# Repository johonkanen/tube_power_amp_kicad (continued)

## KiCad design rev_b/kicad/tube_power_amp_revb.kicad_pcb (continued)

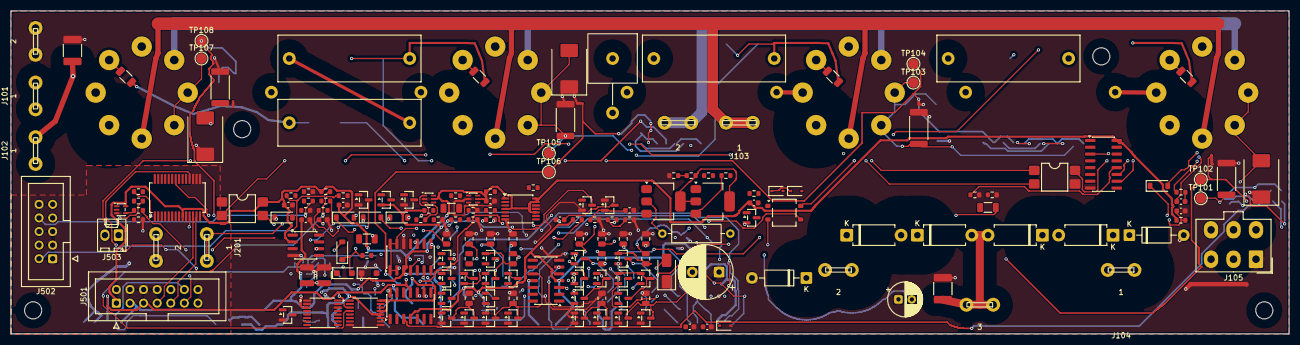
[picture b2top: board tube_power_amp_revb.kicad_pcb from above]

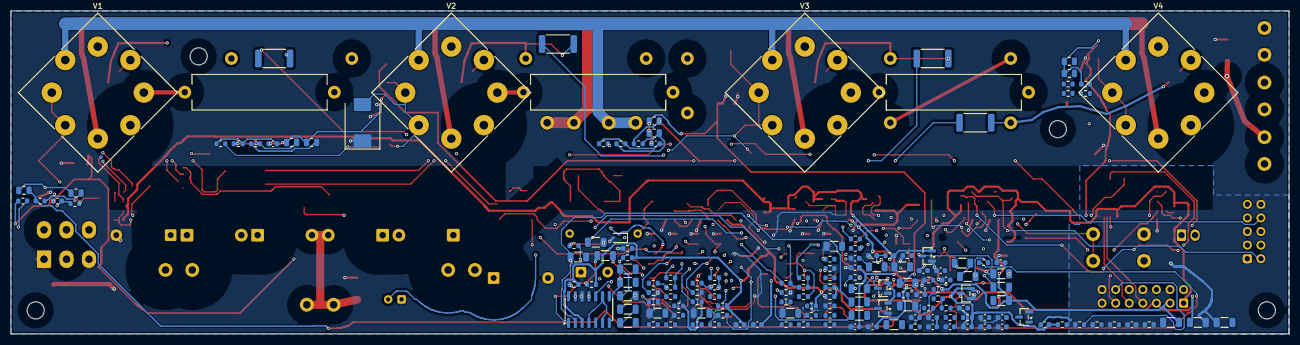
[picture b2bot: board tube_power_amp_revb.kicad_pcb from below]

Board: 4 copper layers, 238.8 x 60.3 mm, 340 parts (158 on the bottom side), 188 nets.

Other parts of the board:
H1, H2, H3, H4: M3 standoff 15 mm

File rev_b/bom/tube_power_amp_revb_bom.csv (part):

refs,qty,value,footprint,candidate part,note
C101 C102,2,100n/630V,Capacitor_SMD:C_1812_4532Metric,100n 630 V X7R 1812,
C103 C104 C105 C106,4,220n/630V MKP,Capacitor_THT:C_Rect_L26.5mm_W8.5mm_P22.50mm_MKS4,"220n 630 V MKP, P 22.5 mm (WIMA MKP4 26.5 x 7 / Kemet R76 class)",body width <= 8.5 mm (layout)
C201,1,100u/100V 105C,Capacitor_THT:CP_Radial_D10.0mm_P5.00mm,"UPW2A101MPD (Nichicon, 105 C)",
C202 C203,2,10u/100V X7S 1210,Capacitor_SMD:C_1210_3225Metric,GRM32EC72A106KE05 (Murata),about 30 % left at 72 V
C204,1,10u/100V 105C,Capacitor_THT:CP_Radial_D6.3mm_P2.50mm,"UPW2A100MED (Nichicon, 105 C)",
C205 C206 C209 C210 C211 C301 C304 C305 C401 C402 C406 C410 C414 C418 C419 C420 C422 C423 C424 C425 C426 C427 C501 C505 C506 C509 C510 C511,28,100n,Capacitor_SMD:C_0603_1608Metric,100n 50 V X7R 0603,
C207 C208 C403 C407 C411 C415,6,10n,Capacitor_SMD:C_0603_1608Metric,10n 50 V X7R 0603,
C212 C302 C303 C421 C507,5,1u,Capacitor_SMD:C_0603_1608Metric,1u 50 V X7R 0603,
C306 C310 C314 C318,4,330n,Capacitor_SMD:C_0805_2012Metric,330n 50 V X7R 0805 (C0G 1206 preferred),
C307 C311 C315 C319,4,100n/100V,Capacitor_SMD:C_0805_2012Metric,100n 100 V X7R / X7S 0805 (GRM21BC72A105 class for 1 uF),
C308 C309 C312 C313 C316 C317 C320 C321,8,1u/100V,Capacitor_SMD:C_0805_2012Metric,1u 100 V X7R / X7S 0805 (GRM21BC72A105 class for 1 uF),
C404 C405 C408 C409 C412 C413 C416 C417,8,220n,Capacitor_SMD:C_0805_2012Metric,220n 50 V X7R 0805 (C0G 1206 preferred),
C502 C503,2,10u/25V,Capacitor_SMD:C_1206_3216Metric,10u/25V X7R 1206,
C504,1,10u/10V,Capacitor_SMD:C_1206_3216Metric,10u/10V X7R 1206,
C508,1,15n,Capacitor_SMD:C_0603_1608Metric,15n 50 V X7R 0603,
D101 D104,2,"RGP02-20E (2 kV, plate diode)",Diode_THT:D_DO-41_SOD81_P10.16mm_Horizontal,"RGP02-20E-E3/54 (Vishay, 2 kV, 0.5 A, 300 ns)",
D102 D103 D105 D106,4,"P6KE350CA (TVS, bidirectional)",Diode_THT:D_DO-15_P10.16mm_Horizontal,"P6KE350CA (Littelfuse; VBR 332-368 V, VC 482 V at 1.24 A)",
D107 D108 D109 D110,4,S3M (3 A),Diode_SMD:D_SMC,S3M-E3/57T (Vishay),
D201,1,S1G (reverse clamp),Diode_SMD:D_SMA,S1G (1N4004 class),
D202 D203,2,BZT52H-B36 (2 %),Diode_SMD:D_SOD-123F,"BZT52H-B36,115 (Nexperia)",1 cm2 cathode copper (150 K/W)
D204,1,1N4148W (speed-up),Diode_SMD:D_SOD-123,1N4148W-7-F (Diodes Inc),
D205 D207,2,BAS416 (low leakage),Diode_SMD:D_SOD-323,"BAS416,115 (Nexperia)",
D206 D208 D209,3,1N4148W,Diode_SMD:D_SOD-123,1N4148W-7-F (Diodes Inc),
D210,1,BAT54S (pump),Package_TO_SOT_SMD:SOT-23,"BAT54S,215 (Nexperia)",
D401 D402 D403 D404,4,"BAV199 (ADC clamp, low leakage)",Package_TO_SOT_SMD:SOT-23,"BAV199,215 (Nexperia)",low leakage
D501,1,MB1S,Package_TO_SOT_SMD:TO-269AA,MB1S (onsemi),
D502,1,BZX84C2V4,Package_TO_SOT_SMD:SOT-23,"BZX84-C2V4,215 (Nexperia)",
D503 D504,2,BAT54,Diode_SMD:D_SOD-323,BAT54J (Nexperia),
D505,1,1N4148W (stop at Q14),Diode_SMD:D_SOD-123,1N4148W-7-F (Diodes Inc),
D506,1,1N4148W (reverse),Diode_SMD:D_SOD-123,1N4148W-7-F (Diodes Inc),
J101,1,W04-b V_ANODE / GND_PWR (4.8 mm tabs),tube_power_amp_revb:BladeTab_4.8mm_x2_P10.20mm_Inline,"2x PCB blade tab 4.8 mm (0.187 in), 2 legs on 5.00 mm, 1.4 mm holes (interfaces.md 4.1); order code to confirm",fully insulated receptacles; in line on 10.2 mm
J102,1,W05-b V_SCREEN (4.8 mm tab),tube_power_amp_revb:BladeTab_4.8mm_x1,"1x PCB blade tab 4.8 mm (0.187 in), 2 legs on 5.00 mm, 1.4 mm holes (interfaces.md 4.1); order code to confirm",fully insulated receptacle
J103,1,W06-b HEATER (6.3 mm tabs),tube_power_amp_revb:BladeTab_6.3mm_x2_P11.50mm,"2x PCB blade tab 6.3 mm (0.250 in), 2 legs on 5.00 mm, 1.4 mm holes (interfaces.md 4.1); order code to confirm",6.4 A; tabs on 11.5 mm
J104,1,W11-a OT_A / OT_B / OT_CT (4.8 mm tabs),tube_power_amp_revb:BladeTab_4.8mm_x3_OT,"3x PCB blade tab 4.8 mm (0.187 in), 2 legs on 5.00 mm, 1.4 mm holes (interfaces.md 4.1); order code to confirm","OT_A / OT_CT / OT_B at 0 / 26.4 / 52.8 mm, OT_CT 6.5 mm forward"
J105,1,"W24-b DRIVE (Mini-Fit Jr 2x3, 600 V; 280-390 V DC on pins 2 / 4)",Connector_Molex:Molex_Mini-Fit_Jr_5566-06A_2x03_P4.20mm_Vertical,Molex 39-28-1063 class (Mini-Fit Jr 5566-06A; order code to confirm),"600 V AC/DC; housing 39-01-2060, terminals 39-00-0039; circuit 6 N/C"
J201,1,W09-b -80V / BIAS_RTN (4.8 mm tabs),tube_power_amp_revb:BladeTab_4.8mm_x2_P9.50mm,"2x PCB blade tab 4.8 mm (0.187 in), 2 legs on 5.00 mm, 1.4 mm holes (interfaces.md 4.1); order code to confirm",fully insulated receptacles
J501,1,W14-b CONTROL (template 2x7),Connector_IDC:IDC-Header_2x07_P2.54mm_Vertical,61201421621 (Wurth),"shrouded, keyed"
J502,1,W15-b BIAS (2x5),Connector_IDC:IDC-Header_2x05_P2.54mm_Vertical,61201021621 (Wurth),"shrouded, keyed"
J503,1,W16-a HV_PERMIT+ / HV_PERMIT- (Lock-2.54),Connector_Molex:Molex_KK-254_AE-6410-02A_1x02_P2.54mm_Vertical,22-27-2021 (Molex KK-254),
N101 N102 N103 N104,4,Kelvin at shunt pad,NetTie:NetTie-2_SMD_Pad0.5mm,,Kelvin tap at the shunt pad
Q201 Q202,2,BSP92P (250 V),Package_TO_SOT_SMD:SOT-223-3_TabPin2,BSP92P H6327 (Infineon),250 V
Q203 Q301 Q302 Q303 Q308 Q309 Q314 Q315 Q320 Q321,10,2N7002,Package_TO_SOT_SMD:SOT-23,"2N7002,215 (Nexperia)",
Q304 Q310 Q316 Q322 Q501 Q503,6,MMBT3904,Package_TO_SOT_SMD:SOT-23,MMBT3904 (Nexperia),
Q305 Q306 Q311 Q312 Q317 Q318 Q323 Q324,8,MMBTA92,Package_TO_SOT_SMD:SOT-23,MMBTA92 (300 V),
Q307 Q313 Q319 Q325,4,MMBTA42,Package_TO_SOT_SMD:SOT-23,MMBTA42 (300 V),
Q502,1,MMBT3906,Package_TO_SOT_SMD:SOT-23,MMBT3906 (Nexperia),
R101 R105 R109 R113,4,91k,Resistor_SMD:R_2512_6332Metric,"91k 1 % 2512 high-voltage thick film, >= 500 V working (KOA HV732H / Vishay CRHV class)",grid leak; -240 V blocking transient across it (layout 2026-11-24: SMD on the B side)
R102 R106 R110 R114,4,5.6k,Resistor_SMD:R_1206_3216Metric,5.6k 1 % 1206 (200 V),"grid stopper inside the socket's pin circle, at pin 5 (layout)"
R103 R107 R115,3,1k 5W flameproof,Resistor_THT:R_Axial_Power_L25.0mm_W6.4mm_P27.94mm,"1k 5 W flameproof metal oxide (25 x 6.4 mm, as rev A)","layout 2026-11-24: mounted lying on the B (plate) side, body raised 2 mm, hand-soldered"
R104 R108 R112 R116,4,1R 1W,Resistor_SMD:R_2512_6332Metric,1R 1 W 1 % 50 ppm/K metal strip (2512),
R111,1,1k 5W flameproof,tube_power_amp_revb:R_Axial_Power_L25.0mm_W9.0mm_P10.16mm_Vertical_Tight,"1k 5 W flameproof metal oxide, standing",V3's screen resistor stands on F in the V2-V3 gap (no room for a lying one)
R201,1,10R 1W fusible wirewound,Resistor_THT:R_Axial_DIN0309_L9.0mm_D3.2mm_P12.70mm_Horizontal,CRF251-4 / CRF110 10R (Yageo Vitrohm),"fusible wirewound; inrush of C201 (8 A peak, 0.32 J) to confirm"
R202,1,3.3k 1206,Resistor_SMD:R_1206_3216Metric,3.3k 1 % 1206,
R203 R206 R225 R229 R232 R427 R428 R430 R432 R433 R502 R504 R505 R508 R519 R520 R522,17,100k,Resistor_SMD:R_0603_1608Metric,100k 1 % 0603,
R204 R205 R503,3,10R,Resistor_SMD:R_0603_1608Metric,10R 1 % 0603,
R207 R402 R403 R408 R409 R414 R415 R420 R421,9,47k,Resistor_SMD:R_0603_1608Metric,47k 1 % 0603,
R208,1,1.0k,Resistor_SMD:R_1206_3216Metric,1.0k 1 % 1206,
R209 R210,2,10k 0.1%,Resistor_SMD:R_1206_3216Metric,10k 0.1 % 25 ppm/K thin film 1206,
R211,1,169k 0.1%,Resistor_SMD:R_1206_3216Metric,169k 0.1 % 25 ppm/K thin film 1206,
R212,1,234k 0.1%,Resistor_SMD:R_1206_3216Metric,234k 0.1 % 25 ppm/K thin film 1206,
R213,1,29.4k 0.1%,Resistor_SMD:R_1206_3216Metric,29.4k 0.1 % 25 ppm/K thin film 1206,
R214,1,3.57M,Resistor_SMD:R_1206_3216Metric,3.57M 1 % 1206,
R215 R219 R221 R222 R224 R227 R301 R302 R313 R324 R335 R401 R407 R413 R419 R501 R518 R524 R526 R528 R530,21,10k,Resistor_SMD:R_0603_1608Metric,10k 1 % 0603,
R216,1,271k 0.1%,Resistor_SMD:R_1206_3216Metric,271k 0.1 % 25 ppm/K thin film 1206,
R217,1,16.9k 0.1%,Resistor_SMD:R_1206_3216Metric,16.9k 0.1 % 25 ppm/K thin film 1206,
R218,1,7.32M,Resistor_SMD:R_1206_3216Metric,7.32M 1 % 1206,
R220,1,42.2k,Resistor_SMD:R_0603_1608Metric,42.2k 1 % 0603,
R223,1,2.37M,Resistor_SMD:R_1206_3216Metric,2.37M 1 % 1206,
R226 R310 R311 R321 R322 R332 R333 R343 R344,9,22k,Resistor_SMD:R_0603_1608Metric,22k 1 % 0603,
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
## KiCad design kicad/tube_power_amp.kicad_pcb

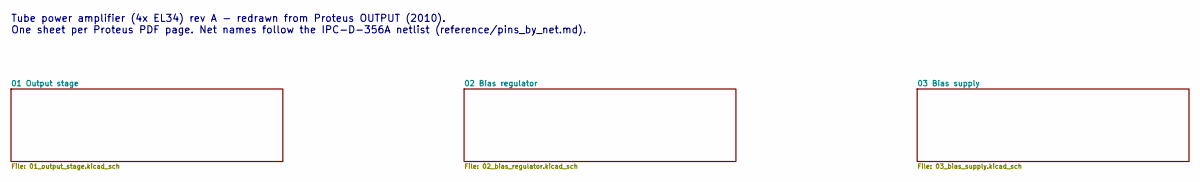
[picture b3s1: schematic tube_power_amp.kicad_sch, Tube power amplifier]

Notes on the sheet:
Tube power amplifier (4x EL34) rev A - redrawn from Proteus OUTPUT (2010). One sheet per Proteus PDF page. Net names follow the IPC-D-356A netlist (reference/pins_by_net.md).

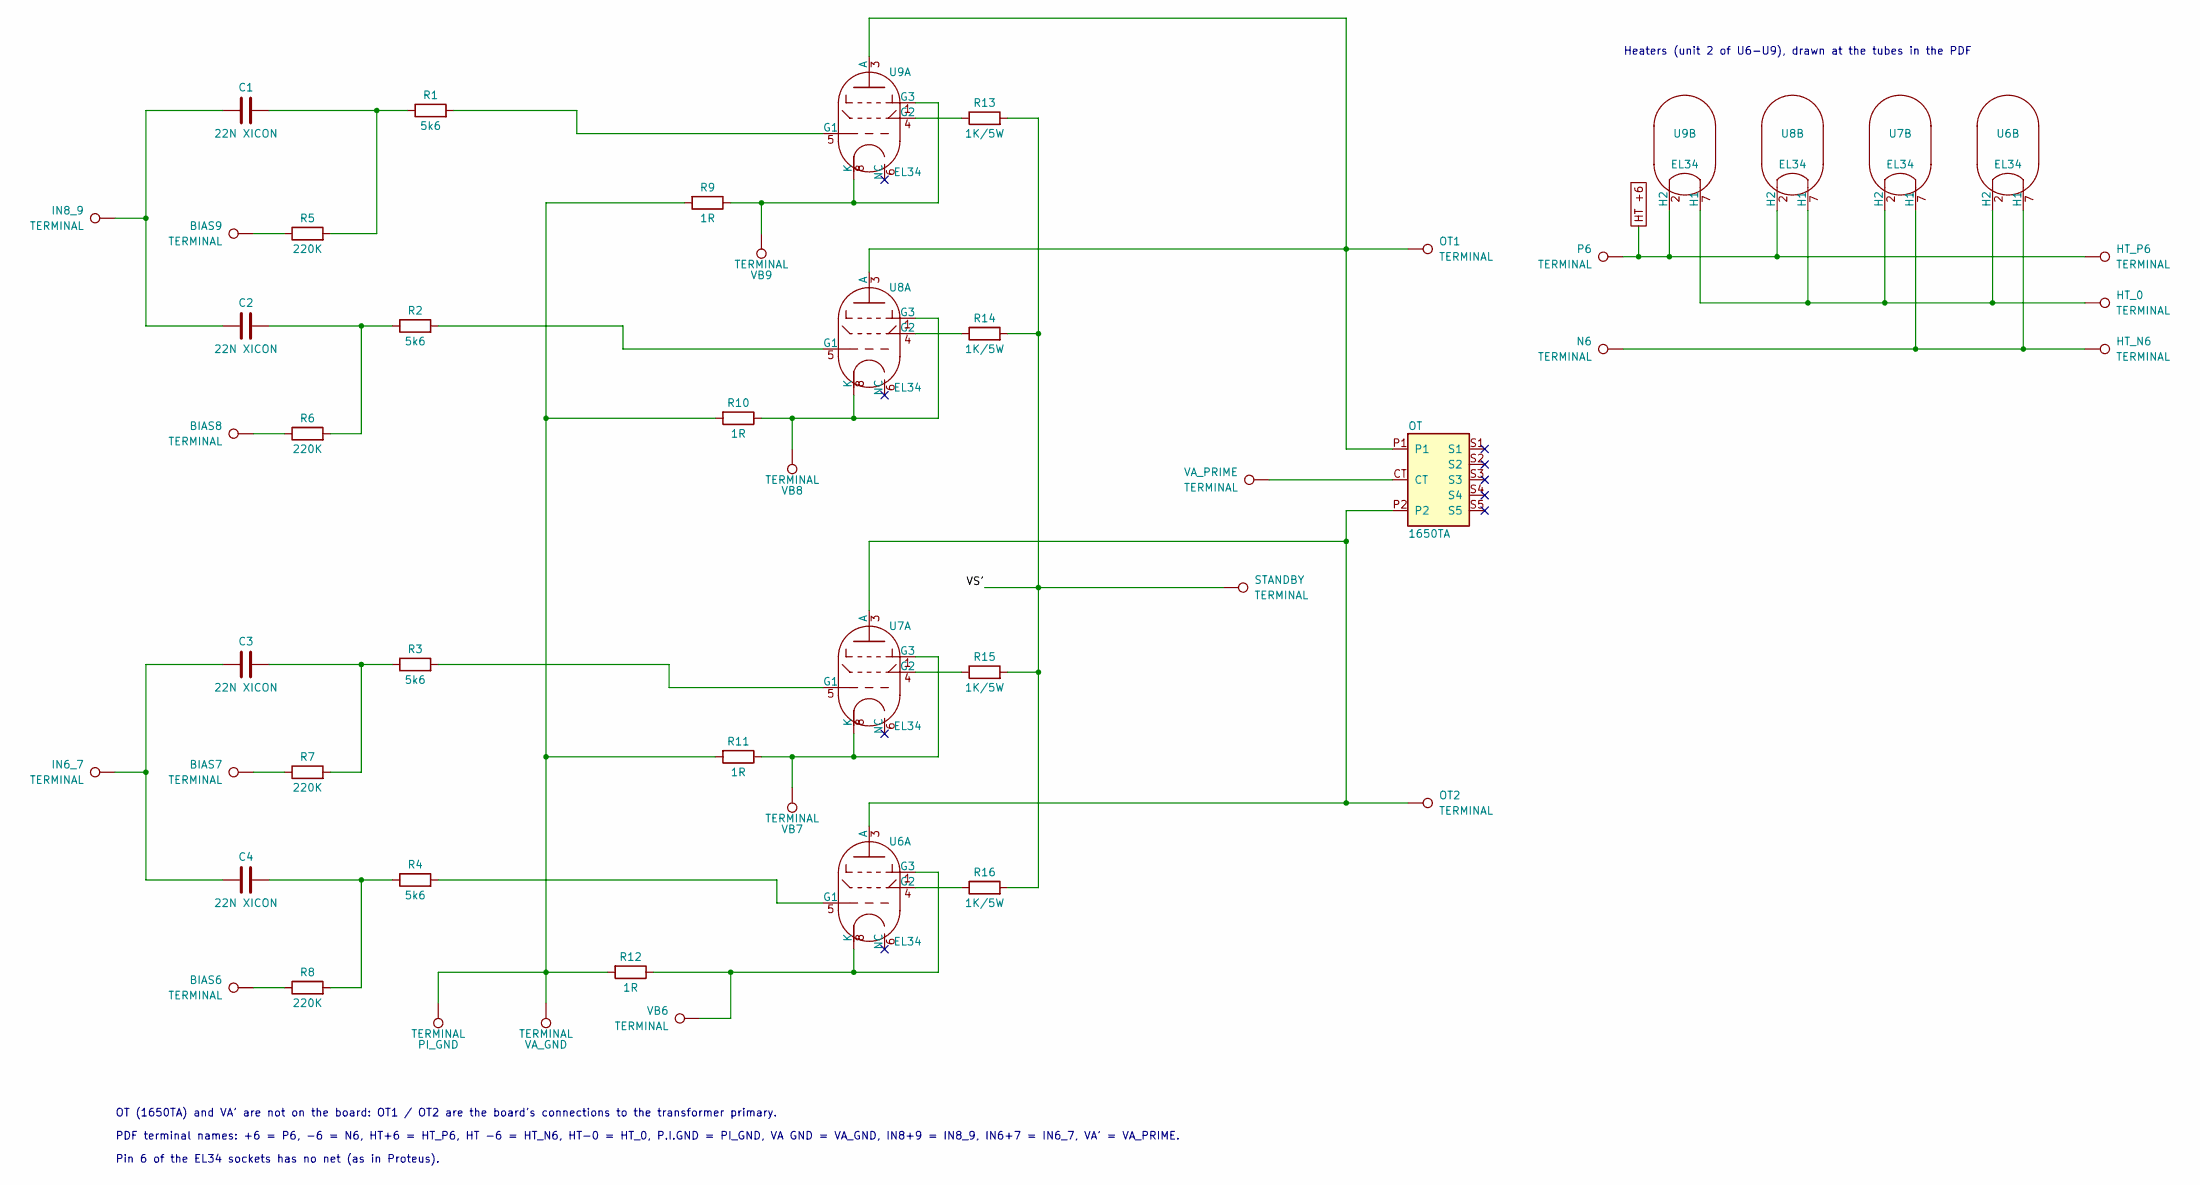
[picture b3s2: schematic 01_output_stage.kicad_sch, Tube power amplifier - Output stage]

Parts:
BIAS6, BIAS7, BIAS8, BIAS9: TERMINAL; FlyLead_Pad_D3.048mm_Drill1.524mm
C1, C2, C3, C4: 22N XICON; C_Rect_L13.0mm_W6.0mm_P9.70mm
HT_0: TERMINAL; FlyLead_Pad_D3.048mm_Drill1.524mm
HT_N6: TERMINAL; FlyLead_Pad_D3.048mm_Drill1.524mm
HT_P6: TERMINAL; FlyLead_Pad_D3.048mm_Drill1.524mm
IN6_7, IN8_9: TERMINAL; FlyLead_Pad_D3.048mm_Drill1.524mm
N6: TERMINAL; FlyLead_Pad_D3.048mm_Drill1.524mm
OT: 1650TA
OT1, OT2: TERMINAL; FlyLead_Pad_D3.048mm_Drill1.524mm
P6: TERMINAL; FlyLead_Pad_D3.048mm_Drill1.524mm
PI_GND: TERMINAL; FlyLead_Pad_D3.048mm_Drill1.524mm
R1, R2, R3, R4: 5k6; R_Axial_DIN0207_L6.3mm_D2.5mm_P10.16mm_Horizontal
R5, R6, R7, R8: 220K; R_Axial_DIN0207_L6.3mm_D2.5mm_P10.16mm_Horizontal
R9, R10, R11, R12: 1R; R_Axial_DIN0207_L6.3mm_D2.5mm_P10.16mm_Horizontal
R13, R14, R15, R16: 1K/5W; R_Axial_Power_L25.0mm_W6.4mm_P30.00mm
STANDBY: TERMINAL; FlyLead_Pad_D3.048mm_Drill1.524mm
U6, U7, U8, U9: EL34; Valve_Octal_Belton_PCD17.20mm
VA_GND: TERMINAL; FlyLead_Pad_D3.048mm_Drill1.524mm
VA_PRIME: TERMINAL
VB6, VB7, VB8, VB9: TERMINAL; FlyLead_Pad_D3.048mm_Drill1.524mm

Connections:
/01 Output stage/VS': R13.2, R14.2, R15.2, R16.2, STANDBY.1
HT +6: HT_P6.1, P6.1, U8.2 (H2), U9.2 (H2); also elsewhere on the board
unnamed: BIAS6.1, R8.1
unnamed: BIAS7.1, R7.1
unnamed: BIAS8.1, R6.1
unnamed: BIAS9.1, R5.1
unnamed: C1.1, C2.1, IN8_9.1
unnamed: C1.2, R1.1, R5.2
unnamed: C2.2, R2.1, R6.2
unnamed: C3.1, C4.1, IN6_7.1
unnamed: C3.2, R3.1, R7.2
unnamed: C4.2, R4.1, R8.2
unnamed: OT.CT, VA_PRIME.1
unnamed: PI_GND.1, R9.2, R10.2, R11.2, R12.2, VA_GND.1
unnamed: OT.P2, OT2.1, U6.3 (A), U7.3 (A)
unnamed: R4.2, U6.5 (G1)
unnamed: R16.1, U6.4 (G2)
unnamed: R12.1, U6.1 (G3), U6.8 (K), VB6.1
unnamed: HT_N6.1, N6.1, U6.7 (H1), U7.7 (H1)
unnamed: HT_0.1, U6.2 (H2), U7.2 (H2), U8.7 (H1), U9.7 (H1)
unnamed: R3.2, U7.5 (G1)
unnamed: R15.1, U7.4 (G2)
unnamed: R11.1, U7.1 (G3), U7.8 (K), VB7.1
unnamed: OT.P1, OT1.1, U8.3 (A), U9.3 (A)
unnamed: R2.2, U8.5 (G1)
unnamed: R14.1, U8.4 (G2)
unnamed: R10.1, U8.1 (G3), U8.8 (K), VB8.1
unnamed: R1.2, U9.5 (G1)
unnamed: R13.1, U9.4 (G2)
unnamed: R9.1, U9.1 (G3), U9.8 (K), VB9.1

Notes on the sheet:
Heaters (unit 2 of U6-U9), drawn at the tubes in the PDF
OT (1650TA) and VA' are not on the board: OT1 / OT2 are the board's connections to the transformer primary.
PDF terminal names: +6 = P6, -6 = N6, HT+6 = HT_P6, HT -6 = HT_N6, HT-0 = HT_0, P.I.GND = PI_GND, VA GND = VA_GND, IN8+9 = IN8_9, IN6+7 = IN6_7, VA' = VA_PRIME.
Pin 6 of the EL34 sockets has no net (as in Proteus).

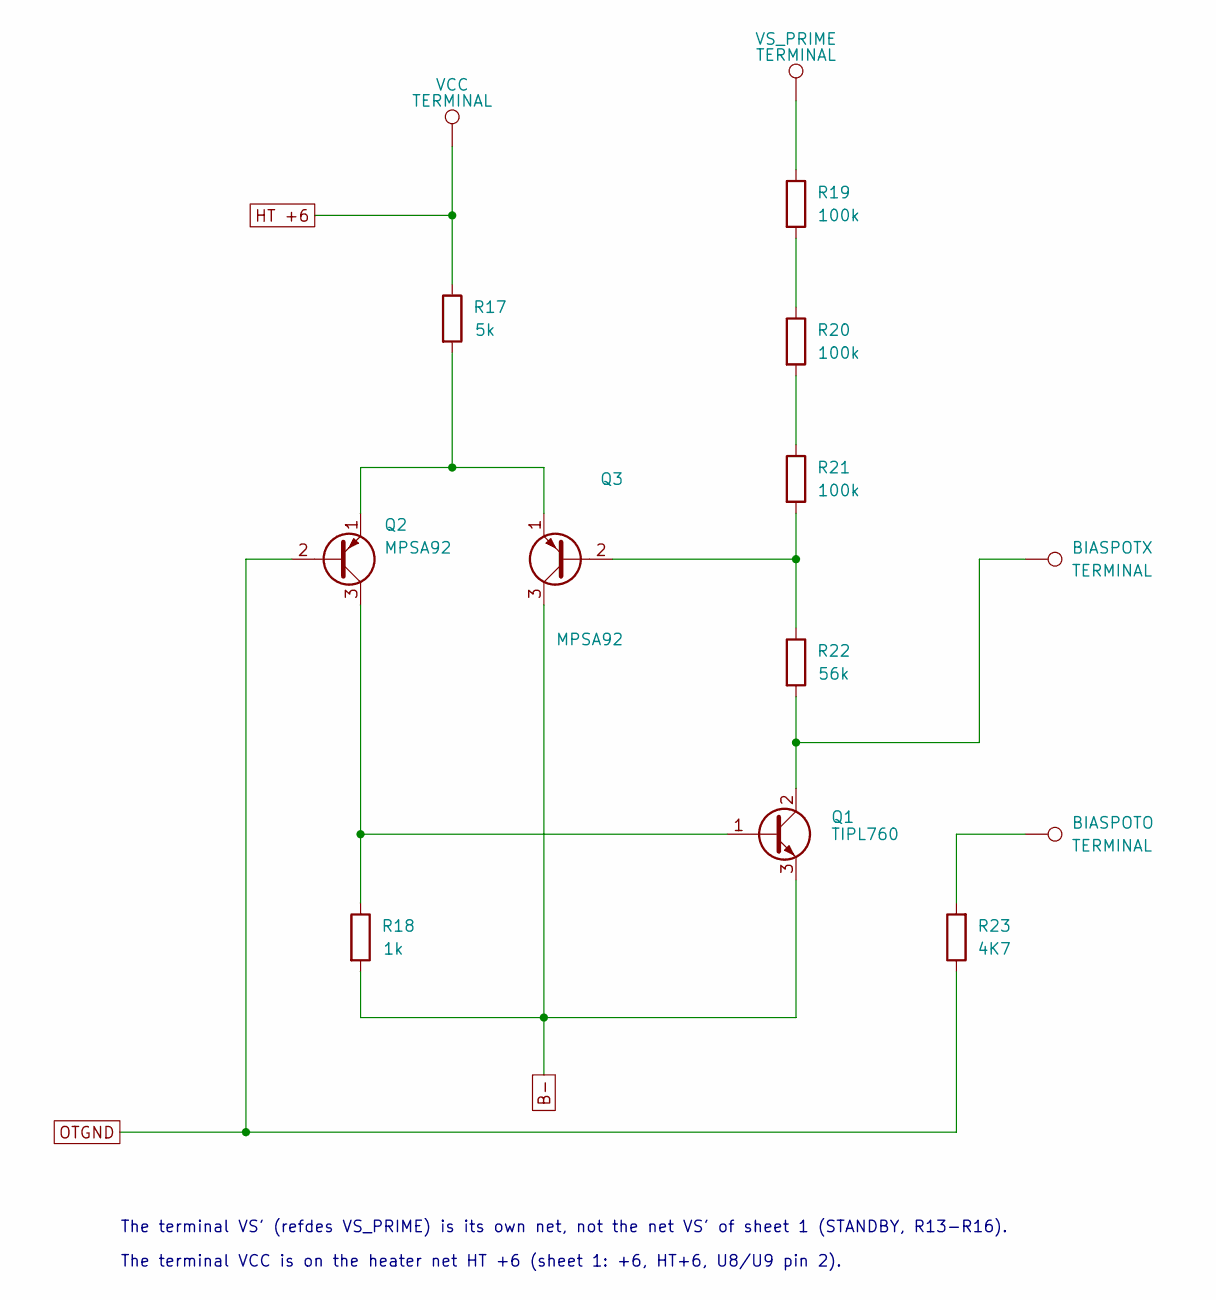
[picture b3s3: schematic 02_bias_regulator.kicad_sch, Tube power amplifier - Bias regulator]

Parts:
BIASPOTO: TERMINAL; FlyLead_Pad_D3.048mm_Drill1.524mm
BIASPOTX: TERMINAL; FlyLead_Pad_D3.048mm_Drill1.524mm
Q1: TIPL760; TO-220-3_Vertical
Q2, Q3: MPSA92; TO-92_Inline_P2.03mm
R17: 5k; R_Axial_DIN0207_L6.3mm_D2.5mm_P10.16mm_Horizontal
R18: 1k; R_Axial_DIN0207_L6.3mm_D2.5mm_P10.16mm_Horizontal
R19, R20, R21: 100k; R_Axial_DIN0207_L6.3mm_D2.5mm_P10.16mm_Horizontal
R22: 56k; R_Axial_DIN0207_L6.3mm_D2.5mm_P10.16mm_Horizontal
R23: 4K7; R_Axial_DIN0207_L6.3mm_D2.5mm_P10.16mm_Horizontal
VCC: TERMINAL; FlyLead_Pad_D3.048mm_Drill1.524mm
VS_PRIME: TERMINAL; FlyLead_Pad_D3.048mm_Drill1.524mm

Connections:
B-: Q1.3 (E), Q3.3 (C), R18.2; also elsewhere on the board
HT +6: R17.1, VCC.1; also elsewhere on the board
unnamed: BIASPOTO.1, R23.2
unnamed: Q1.1 (B), Q2.3 (C), R18.1
unnamed: BIASPOTX.1, Q1.2 (C), R22.2
unnamed: Q2.1 (E), Q3.1 (E), R17.2
unnamed: Q3.2 (B), R21.2, R22.1
unnamed: R19.1, VS_PRIME.1
unnamed: R19.2, R20.1
unnamed: R20.2, R21.1
OTGND: Q2.2 (B), R23.1; also elsewhere on the board

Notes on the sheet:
The terminal VS' (refdes VS_PRIME) is its own net, not the net VS' of sheet 1 (STANDBY, R13-R16).
The terminal VCC is on the heater net HT +6 (sheet 1: +6, HT+6, U8/U9 pin 2).

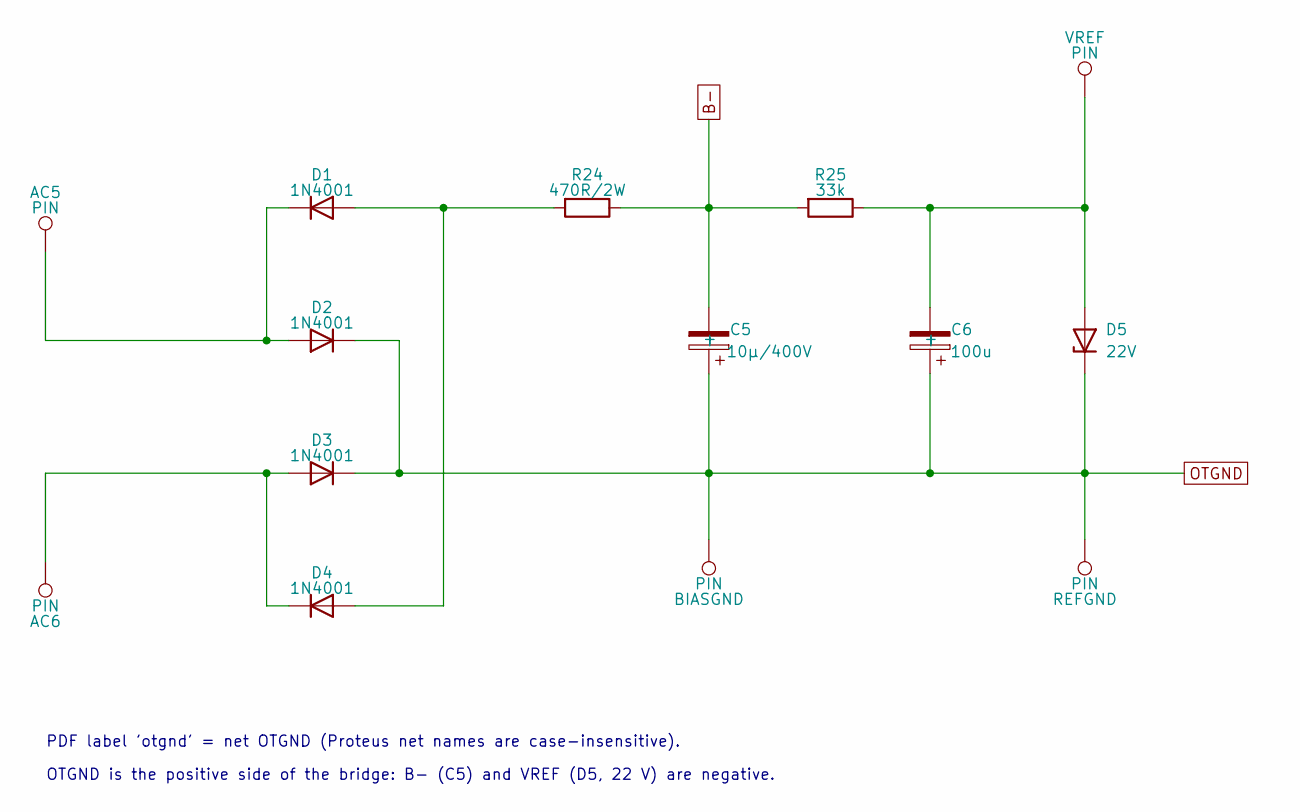
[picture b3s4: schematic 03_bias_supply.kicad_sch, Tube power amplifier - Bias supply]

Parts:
AC5, AC6: PIN; FlyLead_Pad_D3.048mm_Drill1.524mm
BIASGND: PIN; FlyLead_Pad_D3.048mm_Drill1.524mm
C5: 10µ/400V; CP_Radial_D10.0mm_P5.00mm_PM
C6: 100u; CP_Radial_D10.0mm_P5.08mm_PM
D1, D2, D3, D4: 1N4001; D_DO-41_SOD81_P10.16mm_Horizontal_AK
D5: 22V; D_DO-41_SOD81_P10.16mm_Horizontal_AK
R24: 470R/2W; R_Axial_DIN0414_L11.9mm_D4.5mm_P19.05mm_Horizontal
R25: 33k; R_Axial_DIN0414_L11.9mm_D4.5mm_P19.05mm_Horizontal
REFGND: PIN; FlyLead_Pad_D3.048mm_Drill1.524mm
VREF: PIN; FlyLead_Pad_D3.048mm_Drill1.524mm

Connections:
B-: C5.-, R24.1, R25.2; also elsewhere on the board
unnamed: AC5.1, D1.K, D2.A
unnamed: AC6.1, D3.A, D4.K
unnamed: C6.-, D5.A, R25.1, VREF.1
unnamed: D1.A, D4.A, R24.2
OTGND: BIASGND.1, C5.+, C6.+, D2.K, D3.K, D5.K, REFGND.1; also elsewhere on the board

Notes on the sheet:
PDF label 'otgnd' = net OTGND (Proteus net names are case-insensitive).
OTGND is the positive side of the bridge: B- (C5) and VREF (D5, 22 V) are negative.

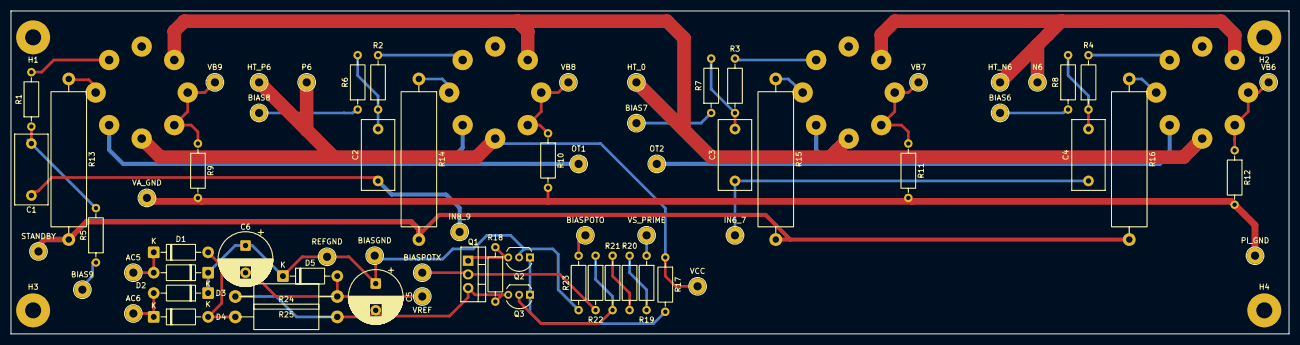
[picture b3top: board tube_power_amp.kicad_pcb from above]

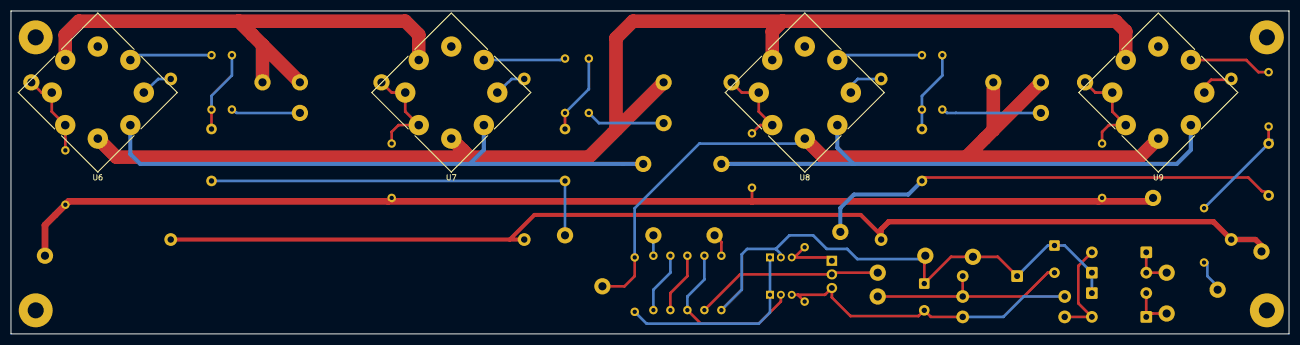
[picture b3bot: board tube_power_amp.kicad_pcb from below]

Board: 2 copper layers, 238.8 x 60.3 mm, 76 parts (4 on the bottom side), 43 nets.

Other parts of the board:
H1, H2, H3, H4: MountingHole_3.0mm; MountingHole_3.0mm_PTH_Pad6.35mm

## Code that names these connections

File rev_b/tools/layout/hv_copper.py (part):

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
What is drawn here (STATUS "Layout, first pass", section "How it is routed"):
- OT_A / OT_B (1.25 kV) on B, 2.0 mm: the lane at y 154.3 in front of the sockets, the rises to the plate
  pins, the branches to the J104 tabs and the clamps; CL_A / CL_B between the TVS pairs.
- V_ANODE: F at the centre tap and the clamps, then In2 along the front edge (y 130.3) and up the east
  strip to J101.
- V_SCREEN: J102 -> F -> via -> In2 "chord" at y 175.2 straight through the four sockets' pin circles
  (between pins 4 / 5 and 7 / 8) with spurs to the four screen resistors and C102.
- G2_1..G2_4 (pin 4 to its screen resistor), DRV_A's run through V2's pin circle (In2, behind the chord),
  the grid leads from the 5.6k stoppers out of the pin circles to the coupling caps.
- The heater pair: HTR1 on F and HTR2 on B stacked along the rear edge (y 185.0, 2.4 mm), the J103 tabs,
  pin 7 (HTR2) stubs on B and the HTR1 leads through each pin circle to pin 2 on F.
- Keep-outs for the router: no tracks / vias / fills on In1 / In2 within 4.2 mm of the OT copper (the
  internal 3.2 mm rule plus the trace), no vias and no B tracks within 7.3 mm of it (6.3 mm + via).
Positions in the chassis frame (layout_frame.py), converted like make_pcb.py.
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
    # ---- OT_A: V1 / V2 plates, lane, branch to the tab and the clamps
    pa1, pa2 = pin(3, sx1), pin(3, sx2)
    ot("OT_A", [pa1, (pa1[0], LANE_Y), (pa2[0], LANE_Y), pa2])
    ja = c.pad("J104", 1, near=(311.7, 139.0))
    d101 = c.pad("D101", 1)
    d102 = c.pad("D102", 1)
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    d104 = c.pad("D104", 1)
    ot("OT_B", [jb0, jb1])
    ot("OT_B", [(xbb, jb0[1]), (xbb, d105[1]), d105])
    ot("OT_B", [(xbb, d105[1]), (372.0, d105[1]), (382.0, LANE_Y), (pin(3, sx4)[0], LANE_Y)])
    ot("OT_B", [jb1, d104])
    for sx in (sx3, sx4):
        p3 = pin(3, sx)
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    lane = [ct1, (ct1[0] + 2.2, 130.3), (507.5, 130.3), (507.5, 166.0), (ja1[0] - 2.5, ja1[1]), ja1]
    c.track("V_ANODE", I1, 2.0, lane)        # In1, the plane layer: In2 carries the plate lanes

    # ---- V_SCREEN: J102 -> F -> via -> In2 chord y 175.2 through the pin circles, spurs
    jv = c.pad("J102", 1, near=(514.5, 163.8))
    c102 = c.pad("C102", 1)
    vx, vy = 507.5, 175.2
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        c.track("V_SCREEN", I2, 0.8, [(p[0], vy), p])

    # ---- G2: pin 4 to its screen resistor
    c.track("G2_1", F, 0.8, [pin(4, sx1), c.pad("R103", 2)])
    c.track("G2_2", F, 0.8, [pin(4, sx2), c.pad("R107", 2)])
    for sx, net, ref in ((sx3, "G2_3", "R111"), (sx4, "G2_4", "R115")):
        p4 = pin(4, sx)
        o, m, i = gap(8, 1, sx, out=2.5, inn=1.5)
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        else:
            c.track(net, F, 0.4, [st, i, m, o, (o[0] + 1.6, 181.4), (cp[0], 181.4), cp])

    # ---- DRV_A through V2's pin circle (In2, behind the V_SCREEN chord): C104 <-> C103
    o56, m56, i56 = gap(5, 6, sx2, out=3.0, inn=2.0)
    o67, m67, i67 = gap(6, 7, sx2, out=3.0, inn=2.0)
    c104, c103 = c.pad("C104", 1), c.pad("C103", 1)
    c.track("DRV_A", I2, 0.6, [c104, (c104[0] - 1.0, o56[1]), o56, m56, i56, i67, m67, o67,
                                (c103[0] + 2.0, o67[1]), c103])

    # ---- DRV_A / DRV_B from J105 (In2): DRV_A through V1's pin circle (pins 1-2 -> 4-5) to C103; DRV_B
    # through it (8-1 -> 5-6), along the rear edge (In2, y 184.5) to C105, and on F to C106
    j2, j4 = c.pad("J105", 2), c.pad("J105", 4)
    o12, m12, i12 = gap(1, 2, sx1, out=2.5, inn=1.5)
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                               (o56b[0] + 0.6, 184.5), (c105[0] - 0.6, 184.5), c105])
    c.track("DRV_B", F, 0.6, [c105, c106])

    # ---- heater pair: HTR1 F / HTR2 B stacked at the rear edge, pin 7 stubs (B), HTR1 to pin 2 (F)
    HY, HW = 185.0, 2.4
    g1, g4 = gap(6, 7, sx1)[1][0], gap(6, 7, sx4)[1][0]
    c.track("HTR1", F, HW, [(g1, HY), (g4, HY)])
    c.track("HTR2", B, HW, [(pin(7, sx1)[0], HY), (pin(7, sx4)[0], HY)])
    for sx in (sx1, sx2, sx3, sx4):
        p7, p2 = pin(7, sx), pin(2, sx)
        c.track("HTR2", B, 1.2, [(p7[0], HY), p7])
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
